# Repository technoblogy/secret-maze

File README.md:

# Secret Maze
A simple maze game for the ATtiny85.
For more information see http://www.technoblogy.com/show?4NRC.

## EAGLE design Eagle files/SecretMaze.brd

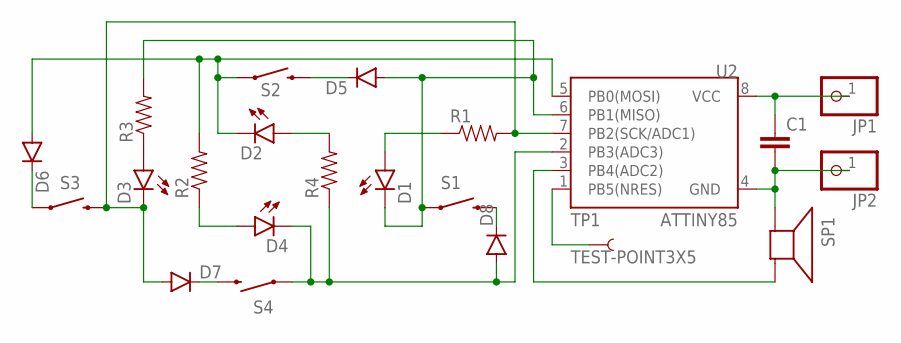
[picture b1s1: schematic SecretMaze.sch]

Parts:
C1: CAP_; AXIAL-5MM
D1, D2, D3, D4: LED5MM
D5, D6, D7, D8: DIODEPTH; DIODE-1N4001
JP1, JP2: PINHD-1X1CB; 1X01-CLEANBIG
R1, R2, R3, R4: RESISTORPTH-1/4W; AXIAL-0.4
S1, S2, S3, S4: SWITCH-MOMENTARY-2PTH; TACTILE-PTH
SP1: SPEAKER/AL60P; AL60P
TP1: TEST-POINT3X5; PAD.03X.05
U2: ATTINY85; DIP08

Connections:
unnamed: D1.K (C), D5.A, R3.P$2 (2), S1.1, U2.6 (PB1(MISO))
unnamed: D7.C, S4.3 (2)
unnamed: SP1.2 (-), U2.3 (PB4(ADC2))
unnamed: D3.K (C), D7.A, R1.P$2 (2), S3.3 (2), U2.7 (PB2(SCK/ADC1))
unnamed: C1.P$2 (2), JP2.1, SP1.1 (+), U2.4 (GND)
unnamed: D8.C, S1.3 (2)
unnamed: D6.C, S3.1
unnamed: D2.A, R4.P$2 (2)
unnamed: D1.A, R1.P$1 (1)
unnamed: D3.A, R3.P$1 (1)
unnamed: D4.A, R2.P$1 (1)
unnamed: C1.P$1 (1), JP1.1, U2.8 (VCC)
unnamed: D5.C, S2.3 (2)
unnamed: TP1.P$1, U2.1 (PB5(NRES))
unnamed: D2.K (C), D6.A, R2.P$2 (2), S2.1, U2.5 (PB0(MOSI))
unnamed: D4.K (C), D8.A, R4.P$1 (1), S4.1, U2.2 (PB3(ADC3))

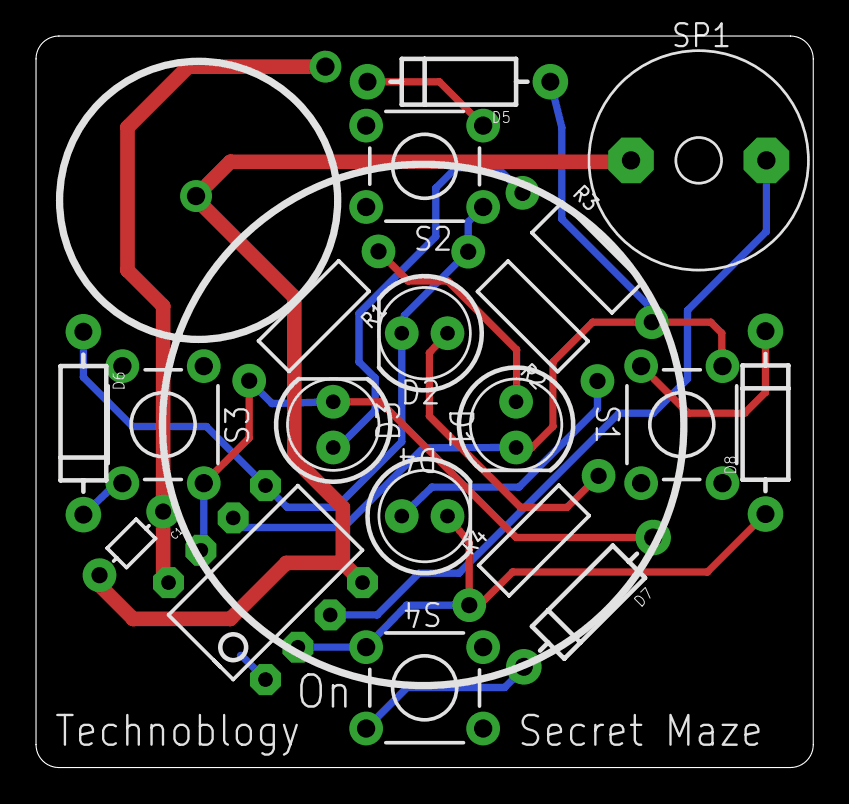
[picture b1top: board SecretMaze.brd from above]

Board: 2 copper layers, 43.2 x 40.6 mm, 22 parts (1 on the bottom side), 16 nets.

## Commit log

2018-03-14 Version 1 - 14th March 2018
2018-03-14 Version 1 - Eagle files
2018-03-24 Version 2 - 24th March 2018
    Returns you to the start of the maze after a short delay when you've successfully reached the goal.
2024-04-15 Version 3 - 15th April 2024

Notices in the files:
parts and their libraries:
SparkFun-LED: Licensing: Creative Commons ShareAlike 4.0 International - https://creativecommons.org/licenses/by-sa/4.0
